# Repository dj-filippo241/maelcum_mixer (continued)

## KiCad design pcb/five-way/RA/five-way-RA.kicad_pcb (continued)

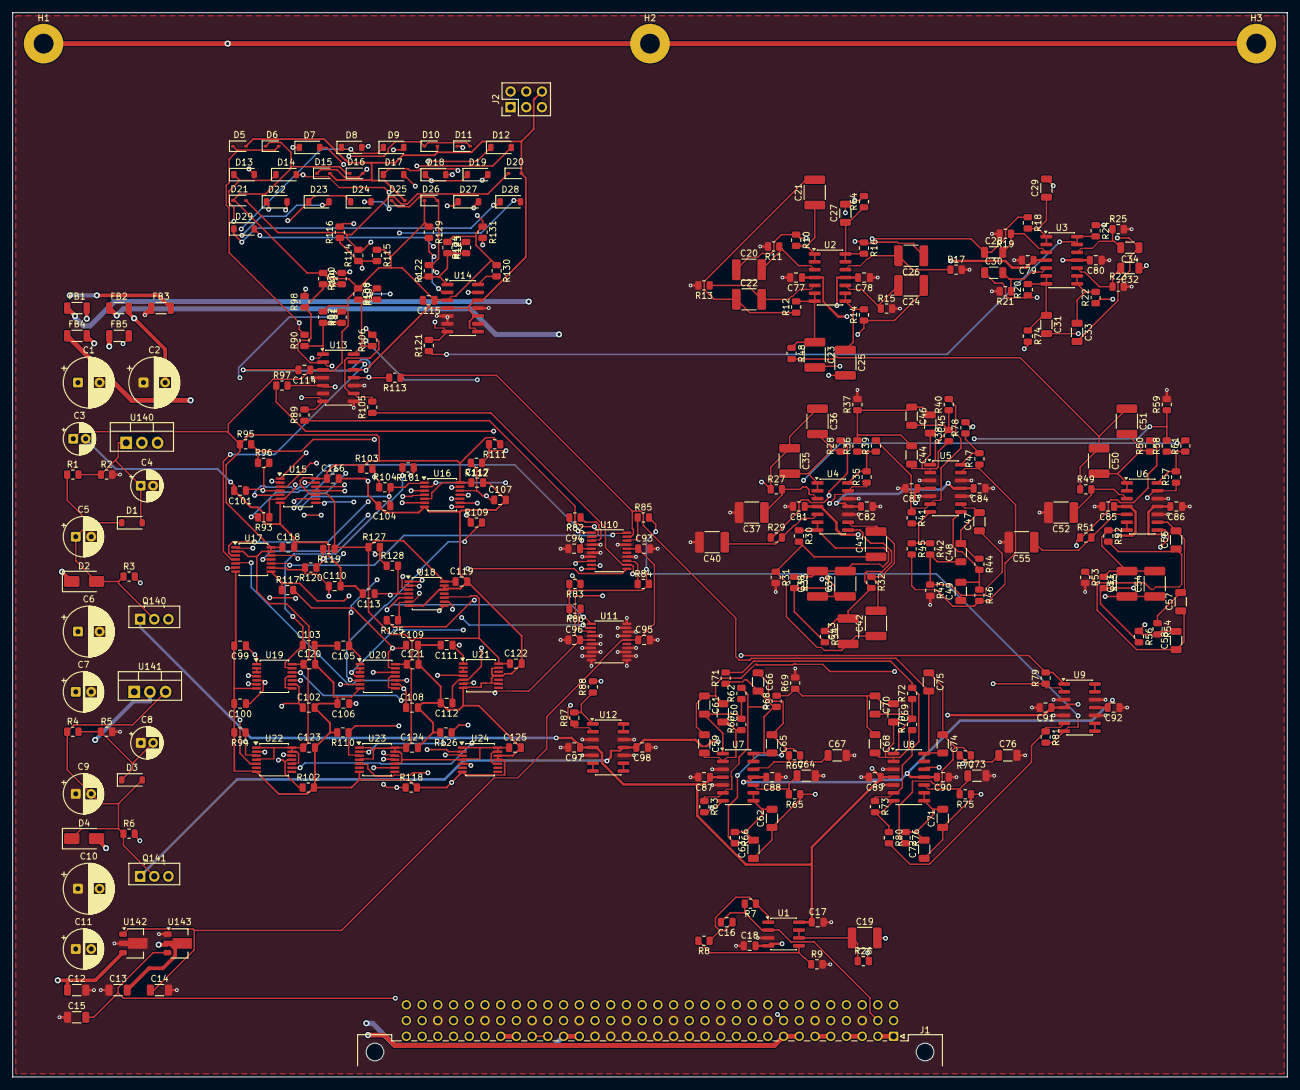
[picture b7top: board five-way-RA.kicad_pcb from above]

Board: 4 copper layers, 206.0 x 172.0 mm, 325 parts (0 on the bottom side), 195 nets.

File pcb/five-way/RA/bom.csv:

quantita;valore;impronta;riferimenti;nota
2;220u 35V;CP_Radial_D8.0mm_P3.50mm;C1 C2;
5;220n;C_0805_2012Metric;C100 C103 C106 C109 C112;tempo massimo ~22 ms (via muta)
2;1u 50V;C_1206_3216Metric;C12 C13;
2;1u 25V;C_1206_3216Metric;C14 C15;
1;22p C0G;C_0805_2012Metric;C16;NOTA: Cf come i ricevitori a massa virtuale del master
41;100n;C_0805_2012Metric;C17 C18 C77 C78 C79 C80 C81 C82 C83 C84 C85 C86 C87 C88 C89 C90 C91 C92 C93 C94 C95 C96 C97 C98 C101 C104 C107 C110 C113 C114 C115 C116 C117 C118 C119 C120 C121 C122 C123 C124 C125;
16;100n film;C_1812_4532Metric;C19 C20 C21 C22 C23 C24 C25 C26 C36 C37 C39 C40 C51 C52 C54 C55;
12;10n C0G;C_1206_3216Metric;C27 C28 C29 C30 C45 C46 C57 C58 C63 C64 C66 C67;
1;47u 10V;CP_Radial_D5.0mm_P2.00mm;C3;
8;4n7 C0G;C_1206_3216Metric;C31 C32 C33 C34 C72 C73 C75 C76;
4;100n film;C_1812_4532Metric;C35 C38 C50 C53;C1 = 2 Cc: due in parallelo (NOTA)
2;10u 35V;CP_Radial_D5.0mm_P2.00mm;C4 C8;
1;47n film;C_1812_4532Metric;C41;C1 = 2C: due in parallelo (NOTA)
2;47n film;C_1812_4532Metric;C42 C43;
2;10n C0G;C_1206_3216Metric;C44 C56;C1 = 2C: due in parallelo (NOTA)
3;1n5 C0G;C_1206_3216Metric;C47 C59 C68;C1 = 2C: due in parallelo (NOTA)
6;1n5 C0G;C_1206_3216Metric;C48 C49 C60 C61 C69 C70;
2;47u 35V;CP_Radial_D6.3mm_P2.50mm;C5 C9;
2;470u 25V;CP_Radial_D8.0mm_P3.50mm;C6 C10;
2;10n C0G;C_1206_3216Metric;C62 C65;C1 = 2 Cc: due in parallelo (NOTA)
2;100u 25V;CP_Radial_D6.3mm_P2.50mm;C7 C11;
2;4n7 C0G;C_1206_3216Metric;C71 C74;C1 = 2 Cc: due in parallelo (NOTA)
5;1n C0G;C_0805_2012Metric;C99 C102 C105 C108 C111;ritardo del fronte ~2 us
1;1N4148W;D_SOD-123;D1;scarica Cadj
1;S1G;D_SMA;D2;protezione inversa
6;1N4148W;D_SOD-123;D3 D9 D14 D19 D24 D29;
1;S1G;D_SMA;D4;
10;BAT54WS;D_SOD-323;D5 D6 D10 D11 D15 D16 D20 D21 D25 D26;
5;1N4148W;D_SOD-123;D7 D12 D17 D22 D27;scarica il tempo massimo
5;1N4148W;D_SOD-123;D8 D13 D18 D23 D28;NOTA: OR a diodi
5;ferrite 600R;L_1206_3216Metric;FB1 FB2 FB3 FB4 FB5;
1;C96 maschio;DIN41612_C_3x32_Male_Horizontal_THT;J1;DIN 41612 C 3x32, angolo retto; lato R del 5-way, parte A
1;2x3 cavo piatto;PinHeader_2x03_P2.54mm_Vertical;J2;cavo piatto corto verso la scheda comandi dietro il pannello (dec. 133)
1;BD139;TO-126-3_Vertical;Q140;
1;BD140;TO-126-3_Vertical;Q141;
2;120 1%;R_0805_2012Metric;R1 R4;
13;18k7 0.1%;R_0805_2012Metric;R10 R12 R19 R21 R26 R27 R28 R29 R37 R43 R53 R59 R69;
2;37k4 0.1%;R_0805_2012Metric;R11 R13;
3;10k;R_0805_2012Metric;R129 R130 R131;uscita libera
6;4k53 0.1%;R_0805_2012Metric;R14 R16 R48 R49 R50 R51;
2;9k09 0.1%;R_0805_2012Metric;R15 R17;
11;9k31 0.1%;R_0805_2012Metric;R18 R20 R36 R42 R52 R58 R64 R65 R66 R67 R68;
1;1k74 1%;R_0805_2012Metric;R2;E96 1,74k = 19,4 V (fx-send NOTE punto 16)
6;3k01 0.1%;R_0805_2012Metric;R22 R24 R74 R75 R76 R77;
2;6k04 0.1%;R_0805_2012Metric;R23 R25;
1;1k;R_0805_2012Metric;R3;NOTA: cap-moltiplicatore come il FX-SEND (~50 mA)
1;9k53 0.1%;R_0805_2012Metric;R30;
1;19k1 0.1%;R_0805_2012Metric;R31;
1;14k3 0.1%;R_0805_2012Metric;R32;
18;10k 0.1%;R_0805_2012Metric;R33 R35 R39 R41 R45 R47 R55 R57 R61 R63 R71 R73 R82 R83 R84 R85 R86 R87;
6;4k99 0.1%;R_0805_2012Metric;R34 R40 R46 R56 R62 R72;NOTA: R/2 = 5k, E192 4,99k (-0,2 %)
5;14k0 0.1%;R_0805_2012Metric;R38 R44 R54 R60 R70;
1;1k74 1%;R_0805_2012Metric;R5;
1;1k;R_0805_2012Metric;R6;
1;10k 0.1%;R_0805_2012Metric;R7;ricevitore a massa virtuale: unity per sorgente (10k lato canale)
2;2k 0.1%;R_0805_2012Metric;R78 R80;invertitore unity, R appaiate (§8.10)
2;2k 0.1%;R_0805_2012Metric;R79 R81;
1;20k 0.1%;R_0805_2012Metric;R8;pad -6 dB (dec. 73)
1;47;R_0805_2012Metric;R88;NOTA: somma delle vie verso la scheda B (b7/b8); 40,2k di carico sulla B
5;22k;R_0805_2012Metric;R89 R97 R105 R113 R121;NOTA: 22k + Schottky: l'ingresso del LM339 resta sopra -0,3 V
1;20k 0.1%;R_0805_2012Metric;R9;
5;10M;R_0805_2012Metric;R90 R98 R106 R114 R122;isteresi ~11 mV sulla via (22k/10M x 5 V)
5;10k;R_0805_2012Metric;R91 R99 R107 R115 R123;
5;2k;R_0805_2012Metric;R92 R100 R108 R116 R124;
10;100k;R_0805_2012Metric;R93 R94 R101 R102 R109 R110 R117 R118 R125 R126;
5;10k;R_0805_2012Metric;R95 R103 R111 R119 R127;levetta di kill verso CTRL_GND sulla scheda comandi (chiusa = kill)
5;10k;R_0805_2012Metric;R96 R104 R112 R120 R128;antirimbalzo 1 ms
1;OPA1612AIDR;SOIC-8_3.9x4.9mm_P1.27mm;U1;ricevitore DJ bus e buffer del pad
2;ADG1434YRUZ;TSSOP-20_4.4x6.5mm_P0.65mm;U10 U11;SPDT: A = IN alto = via passa, B = shunt a massa (Rev. E tabella 9)
1;OPA1654AIDR;SOIC-14_3.9x8.7mm_P1.27mm;U12;somma delle vie
2;LM339DR;SOIC-14_3.9x8.7mm_P1.27mm;U13 U14;comparatori dello zero (ingressi riferiti ad AGND)
1;LM317;TO-220-3_Vertical;U140;
1;LM337;TO-220-3_Vertical;U141;
1;78L15;SOT-89-3;U142;
1;79L15;SOT-89-3;U143;
4;74HC86PW;TSSOP-14_4.4x5mm_P0.65mm;U15 U16 U17 U18;fronti, confronto levetta/stato, inversione del tempo massimo
3;74HC14PW;TSSOP-14_4.4x5mm_P0.65mm;U19 U20 U21;ritardo del fronte e tempo massimo (Schmitt)
8;OPA1654AIDR;SOIC-14_3.9x8.7mm_P1.27mm;U2 U3 U4 U5 U6 U7 U8 U9;banca agli incroci H
3;74HC74PW;TSSOP-14_4.4x5mm_P0.65mm;U22 U23 U24;stato del kill: copia la levetta sull'IN dell'ADG

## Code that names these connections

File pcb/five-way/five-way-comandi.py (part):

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  due le posizioni KSWn va a CTRL_GND della sua scheda A (five-way.py: pull-up 10k, chiusa = kill).
  Polo A = LA, polo B = RA.
- GROWL, pot a 6 sezioni (3 per lato, five-way-module §5bis: miscela + due spinte), lineare:
  miscela 10k (antiorario AGND, cursore DWG, orario DDG); spinta dei bassi, reostato 10k fra GLOW e
  GLR (orario = 0 ohm, antiorario = 10k); spinta dei medi, reostato 5k fra GMID e GMR (uguale).
- NASTRO, pot a 4 sezioni (2 per lato), log A: miscela 10k (antiorario AGND, cursore DWT, orario
  DTP); spinta, reostato 5k fra LSP e LSN (antiorario = 0 ohm, orario = 5k).
  NOTA: i pot a 6 e 4 sezioni con valori diversi per sezione non esistono nella libreria di KiCad;
  il pezzo è da scegliere (classe Alps RK27 a più sezioni, o su ordinazione). Impronta segnaposto:
  un pin header coi capi delle sezioni, al centro dell'albero; il pot si collega coi fili.
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
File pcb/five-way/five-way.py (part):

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    power_ln(d, base=144)
    cv.ref5(d, "U146")
d.power_nets("+18V", "-18V", width=0.4)
d.netclass["CTRL_GND"] = 0.3          # pin TSSOP della logica: pista <= 0,3 mm (canale giro 6-7)

if PARTE == "A":
    # ------------------------------------------------------------ ingresso
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        d.part("D", "Device:D_Schottky", "BAT54WS", "Diode_SMD:D_SOD-323", {"A": "CI" + t, "K": "+5VF"})
        d.R("ZC" + t, "CI" + t, "10M", note="isteresi ~11 mV sulla via (22k/10M x 5 V)")
        d.R("+5VF", "ZC" + t, "10k")
        cmp_pins.append(("CI" + t, "AGND", "ZC" + t))
        d.R("ZC" + t, "ZR" + t, "2k")
        d.C("ZR" + t, "CTRL_GND", "1n C0G", note="ritardo del fronte ~2 us")
        sch_g += [("ZR" + t, "ZN" + t), ("ZN" + t, "ZD" + t)]
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        d.R("KSW" + t, "KD" + t, "10k", note="antirimbalzo 1 ms")
        d.C("KD" + t, "CTRL_GND", "100n")
        ff.append(("KD" + t, "CK" + t, "KQ" + t))
    cmp_pins += [("AGND", "CTRL_GND", "ZCX%d" % k) for k in range(1, 4)]
    for k in range(2):
        q = cmp_pins[4 * k:4 * k + 4]
        p = {"VCC": "+5VF", "GND": "CTRL_GND"}
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    d.R("GREST", "GMC", "9k31 0.1%")
    Cx("GMC", "AGND", "6n8", note="polo 2,5 kHz (9,31k / 6,8n = 2,51 kHz)")
    P.add(("GMC", "GMID", "GMID"))
    # clipper dei bassi: spinta = reostato sul cavo (GLOW -> GLR) + 1k fisso; Rf 47k; 1 / 3 diodi con 470R
    d.R("GLR", "GLGN", "1k 0.1%", note="spinta dei bassi: 1k + reostato 10k sul cavo (11k -> 1k, NOTA)")
    d.R("GLGN", "GLOUT", "47k")
    cv.diode(d, "GLGN", "GLA1")
    d.R("GLA1", "GLOUT", "470")
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    d.R("GLB3", "GLGN", "470")
    P.add(("AGND", "GLGN", "GLOUT"))
    # clipper dei medi: spinta = 4,99k + reostato 5k sul cavo (10k -> 5k); Rf 10k; 3 + 3 diodi con 4,7k
    d.R("GMR", "GMGN", "4k99 0.1%", note="spinta dei medi: 4,99k + reostato 5k sul cavo")
    d.R("GMGN", "GMOUT", "10k")
    cv.diode(d, "GMGN", "GMA1"); cv.diode(d, "GMA1", "GMA2"); cv.diode(d, "GMA2", "GMA3")
    d.R("GMA3", "GMOUT", "4k7")
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    d.R("NU4", "NUS", "20k 0.1%", note="inclinazione dei medi (fmt 1 kHz, rt 3)")
    d.R("NUS", "NE5C", "10k 0.1%")
    Cx("NE5C", "AGND", "5n1")
    # spinta non invertente: Rg 1k, Rf = reostato sul cavo (LSP - LSN) con 7,5k in parallelo
    d.R("LSN", "AGND", "1k 0.1%")
    d.R("LSP", "LSN", "7k5", note="NOTA: reostato 5k // 7,5k = 0..3,0k (+12 dB a fine corsa)")
    P.add(("NUS", "LSN", "LSP"))
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
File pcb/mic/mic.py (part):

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                    continue
                sup = [n for n in c.nets.values() if n and n not in self.masse]
                if len(sup) != 1 or sup[0] not in self.power:
                    continue      # solo i C di un'alimentazione: SETP/SETN lasciano posto al fanout del pin 9
                pins = [k for k, n in sorted(u.nets.items()) if n == sup[0] and k not in used]
                if pins:
                    groups.setdefault(u.ref, []).append((c.ref, pins[0]))
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d.gnd = "AGND"
d.inner_signal = True     # SMD sui due lati (dec. 142): In2 strato di piste, massa piena su In1, come master e canale
d.cluster_gap = 0.8      # 0,5 di default: SMB e MUTE_CV (U7, retro) restavano aperte (todo 248)
d.link_pairs = True   # pin gemelli del C96 (+5V, CTRL_GND): Freerouting li lasciava aperti (todo 248)

from cavo import CAVO as FILI     # ordine dei fili: cavo.py, letto anche dalla scheda comandi

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d.block = "INGRESSO XLR: RFI, clamp, carico 2,32k, bias 2x47k (mic-pre.inc)"
d.part("J", "Connector_Generic:Conn_01x03", "XLR (cavo)", "Connector_PinHeader_2.54mm:PinHeader_1x03_P2.54mm_Vertical",
       {1: "CHASSIS", 2: "XHOT", 3: "XCOLD"}, ref="J3", place=(85, 5, 90),
       note="NOTA: cavo verso l'XLR femmina; pin 1 a CHASSIS al connettore (grounding §4)")
for x, f, i in (("XHOT", "HF", "IH"), ("XCOLD", "CF", "IC")):
    d.part("FB", "Device:FerriteBead_Small", "ferrite 600R", cm.FB, {1: x, 2: f})
    d.C(f, "CHASSIS", "100p C0G", note="RFI verso il telaio")
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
